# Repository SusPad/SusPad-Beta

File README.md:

#### The SusPad is an open-source handheld retro-gaming computer. It is powered by a raspberry pi zero.

#### The purpous of this device is to allow for as much input customization as possible, by allowing the user to swap the physical inputs.

#### You could, for example, have an input module specifically for gameboy games, or another for DOS games, or even another one for Nintendo games. The opportunities are endless!

#### And of course, since this entire project is open source, you can even make your own motules!

#### Now, that begs the question: why is it among us themed?
#### Well, the simple answer to that is because I thought it would be funny to make an actual retro gaming handheld that was among us themed XD.

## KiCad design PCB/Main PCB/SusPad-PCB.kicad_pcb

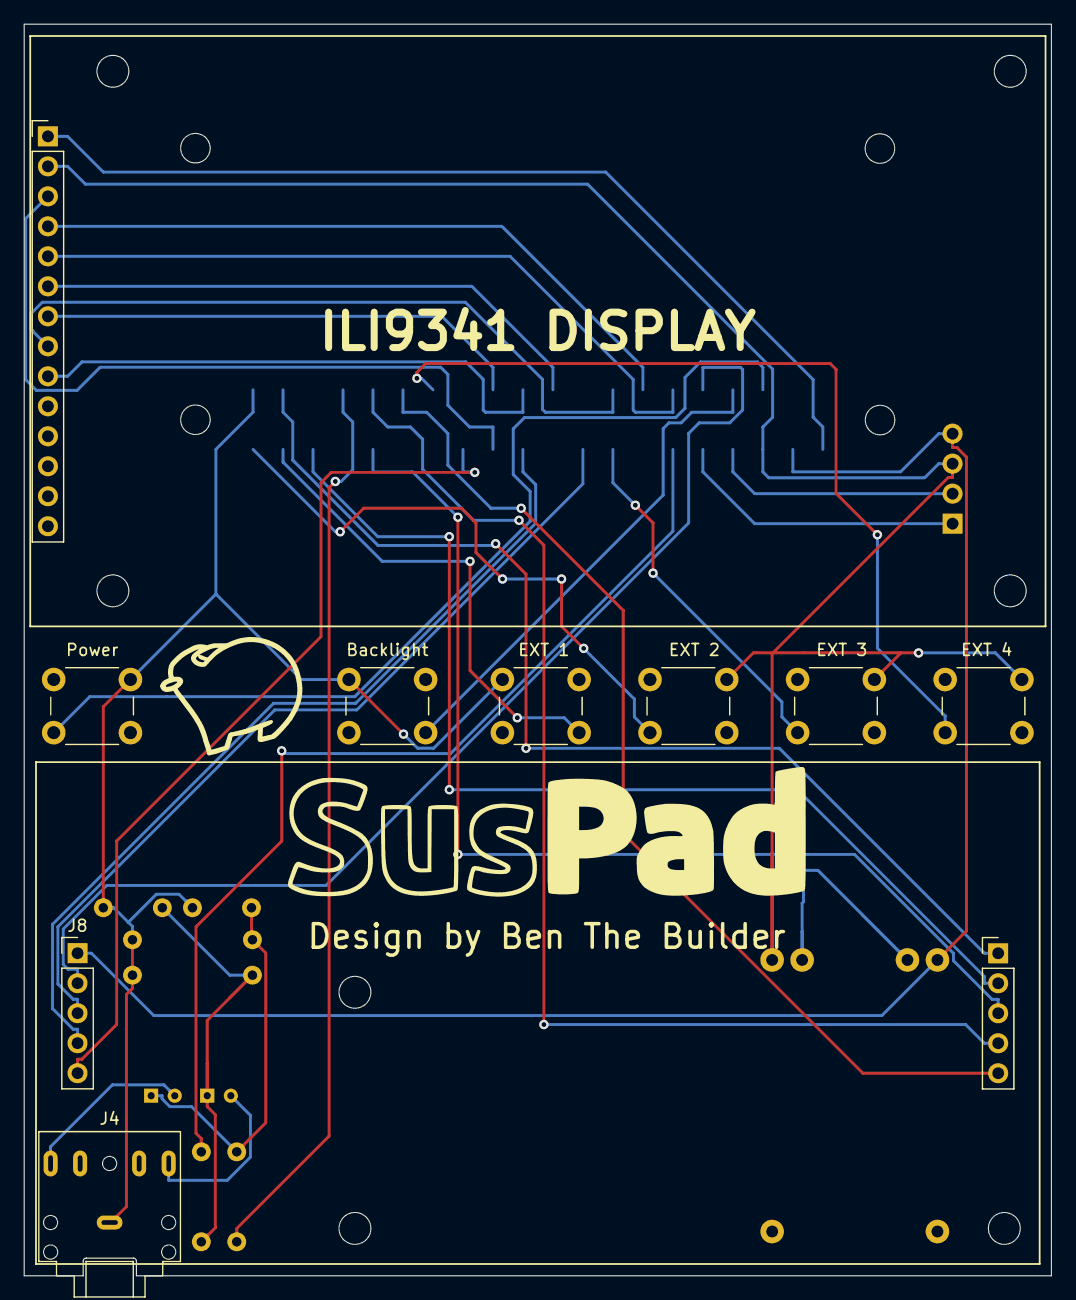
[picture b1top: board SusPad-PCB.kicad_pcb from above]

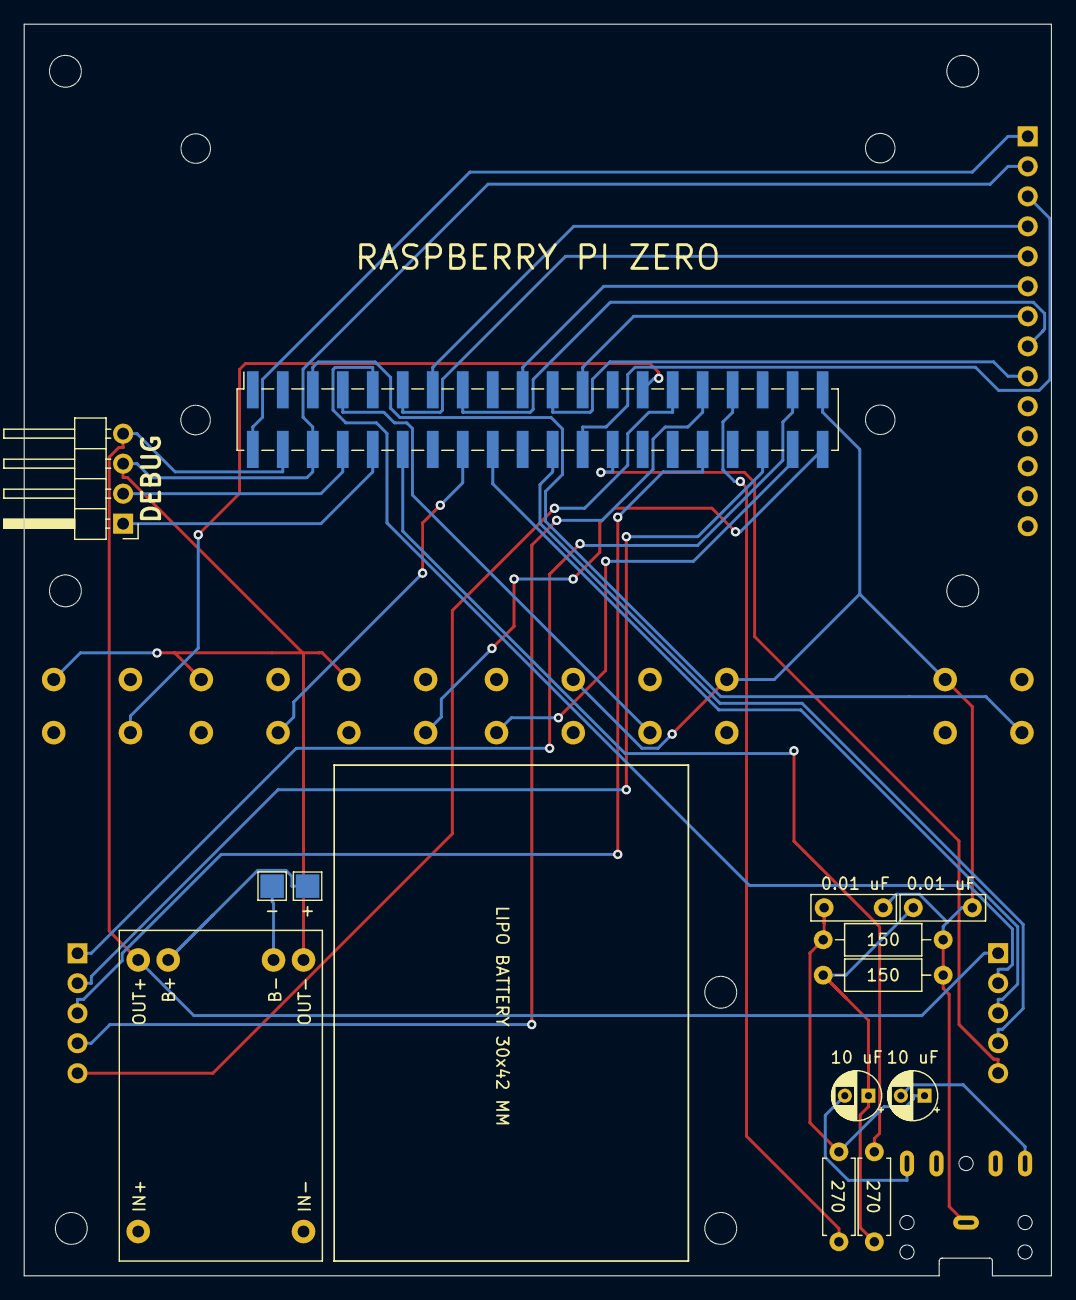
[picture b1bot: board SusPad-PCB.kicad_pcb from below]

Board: 2 copper layers, 87.0 x 106.0 mm, 34 parts (12 on the bottom side), 35 nets.

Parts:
C1, C2: 10 uF; CP_Radial_D4.0mm_P2.00mm
C3, C4: 0.01 uF; C_Rect_L7.0mm_W2.0mm_P5.00mm
J1: Raspberry Pi; PinHeader_2x20_P2.54mm_Vertical_SMD
J2: ILI9341; PinHeader_1x14_P2.54mm_Vertical
J3: Serial Debug; PinHeader_1x04_P2.54mm_Horizontal
J4: Audio Out; Jack_3.5mm_CUI_SJ1-3525N_Horizontal
J5: Battery Charger; TP4056-Module
J6: -; TestPoint_Pad_2.0x2.0mm
J7: +; TestPoint_Pad_2.0x2.0mm
J8: Left I/O; PinHeader_1x05_P2.54mm_Vertical
J9: Right I/O; PinHeader_1x05_P2.54mm_Vertical
R1, R2: 270; R_Axial_DIN0207_L6.3mm_D2.5mm_P7.62mm_Horizontal
R3, R4: 150; R_Axial_DIN0207_L6.3mm_D2.5mm_P10.16mm_Horizontal
REF1, REF3, REF6, REF8, REF9, REF10, REF11: MountingHole_2.7mm_M2.5
REF2, REF4, REF5, REF7: MountingHole_2.5mm
SW1: Power; SW_PUSH_6mm_H4.3mm
SW2: Backlight; SW_PUSH_6mm_H4.3mm
SW3: EXT 1; SW_PUSH_6mm_H4.3mm
SW4: EXT 2; SW_PUSH_6mm_H4.3mm
SW5: EXT 3; SW_PUSH_6mm_H4.3mm
SW6: EXT 4; SW_PUSH_6mm_H4.3mm

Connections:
unnamed: C1.1, C4.1, R2.1, R4.1
unnamed: C1.2, J4.R
unnamed: C2.1, C3.1, R1.1, R3.1
unnamed: C2.2, J4.T
unnamed: C3.2, C4.2, J1.6, J1.39, J2.2, J3.3, J4.S, J5.4, R3.2, R4.2, SW1.1, SW2.1, SW3.1, SW4.1, SW5.1, SW6.1
unnamed: J1.2, J2.1
unnamed: J1.4, J3.4, J5.3, J8.1
unnamed: J1.5, SW1.2
unnamed: J1.7, SW2.2
unnamed: J1.8, J3.2
unnamed: J1.9, J8.2
unnamed: J1.10, J3.1
unnamed: J1.11, J2.5
unnamed: J1.12, R1.2
unnamed: J1.13, J2.4
unnamed: J1.15, J2.8
unnamed: J1.16, SW5.2
unnamed: J1.18, J8.3
unnamed: J1.19, J2.6
unnamed: J1.21, J2.9
unnamed: J1.22, J8.4
unnamed: J1.23, J2.7
unnamed: J1.24, J2.3
unnamed: J1.26, J8.5
unnamed: J1.27, SW6.2
unnamed: J1.29, J9.5
unnamed: J1.31, J9.4
unnamed: J1.32, J9.3
unnamed: J1.33, R2.2
unnamed: J1.36, J9.2
unnamed: J1.37, J9.1
unnamed: J1.38, SW3.2
unnamed: J1.40, SW4.2
unnamed: J5.5, J7.1
unnamed: J5.6, J6.1

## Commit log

2022-10-19 Create e
2022-10-19 Added files
2022-10-20 updated pcb
2022-10-24 restructured repository
2022-10-24 updated stuff
2022-10-25 fixed logo
2022-11-08 updated repo 11/07/22
